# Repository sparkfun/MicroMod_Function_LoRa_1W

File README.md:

SparkFun MicroMod LoRa Function Board
========================================

[*SparkFun MicroMod LoRa Function Board (DEV-18573)*](https://www.sparkfun.com/products/18573)

The SparkFun MicroMod LoRa Function Board provides LoRA and LoRaWAN capabilities to your MicroMod project. It is intended to be used in conjunction with a MicroMod Processor Board and a MicroMod Main Board, which provides the electrical interface between a processor board and the Function Board(s).

The LoRa Function Board utilizes the 915M30S LoRa module from EBYTE, which is a 1W (30dBm) transceiver based around the SX1276 from Semtech. There is a robust edge mount RP-SMA connector for large LoRa (915MHz) antennas; with modification, a U.FL connector is also available. We've successfully tested a 12 miles line-of-sight transmission with this module (test was performed under ideal conditions; individual user results may vary).

With the MicroMod standardization, users no longer need to cross-reference schematics with datasheets, while fumbling around with jumper wires. Simply, match up the function board's M.2 edge connector to the slot of the M.2 connector on the main board and secure the function board with screws.

Repository Contents
-------------------

* **/Firmware** - Arduino example code from the tutorial
* **/Hardware** - Eagle design files (.brd, .sch)
* **/Hardware/Production** - Production panel files (.brd)

Documentation
--------------

* **[E19-915M30S Datasheet](https://github.com/sparkfun/MicroMod_Function_LoRa_1W/blob/main/Documents/E19-915M30S_Usermanual_EN_v1.20.pdf)** - Datasheet for the LoRa module
  * **[SX1276 Datasheet](https://cdn.sparkfun.com/assets/7/7/3/2/2/SX1276_Datasheet.pdf)** - Datasheet for the transceiver the LoRa module is based on
* **[Hookup Guide](https://learn.sparkfun.com/tutorials/1996)** - Basic hookup guide
* **[SparkFun External EEPROM Arduino Library](https://github.com/sparkfun/SparkFun_External_EEPROM_Arduino_Library)** - Arduino library for the EEPROM
* **[RadioLib Arduino Library](https://github.com/jgromes/RadioLib)** - Arduino library for peer-to-peer communication with the LoRa module

Product Versions
----------------

* [DEV-18573](https://www.sparkfun.com/products/18573)- Initial release

Version History
---------------

* v1.0 - Initial Release

License Information
-------------------

This product is _**open source**_! 

Please review the LICENSE.md file for license information. 

If you have any questions or concerns on licensing, please contact technical support on our [SparkFun forums](https://forum.sparkfun.com/viewforum.php?f=152).

Distributed as-is; no warranty is given.

- Your friends at SparkFun.

_<COLLABORATION CREDIT>_

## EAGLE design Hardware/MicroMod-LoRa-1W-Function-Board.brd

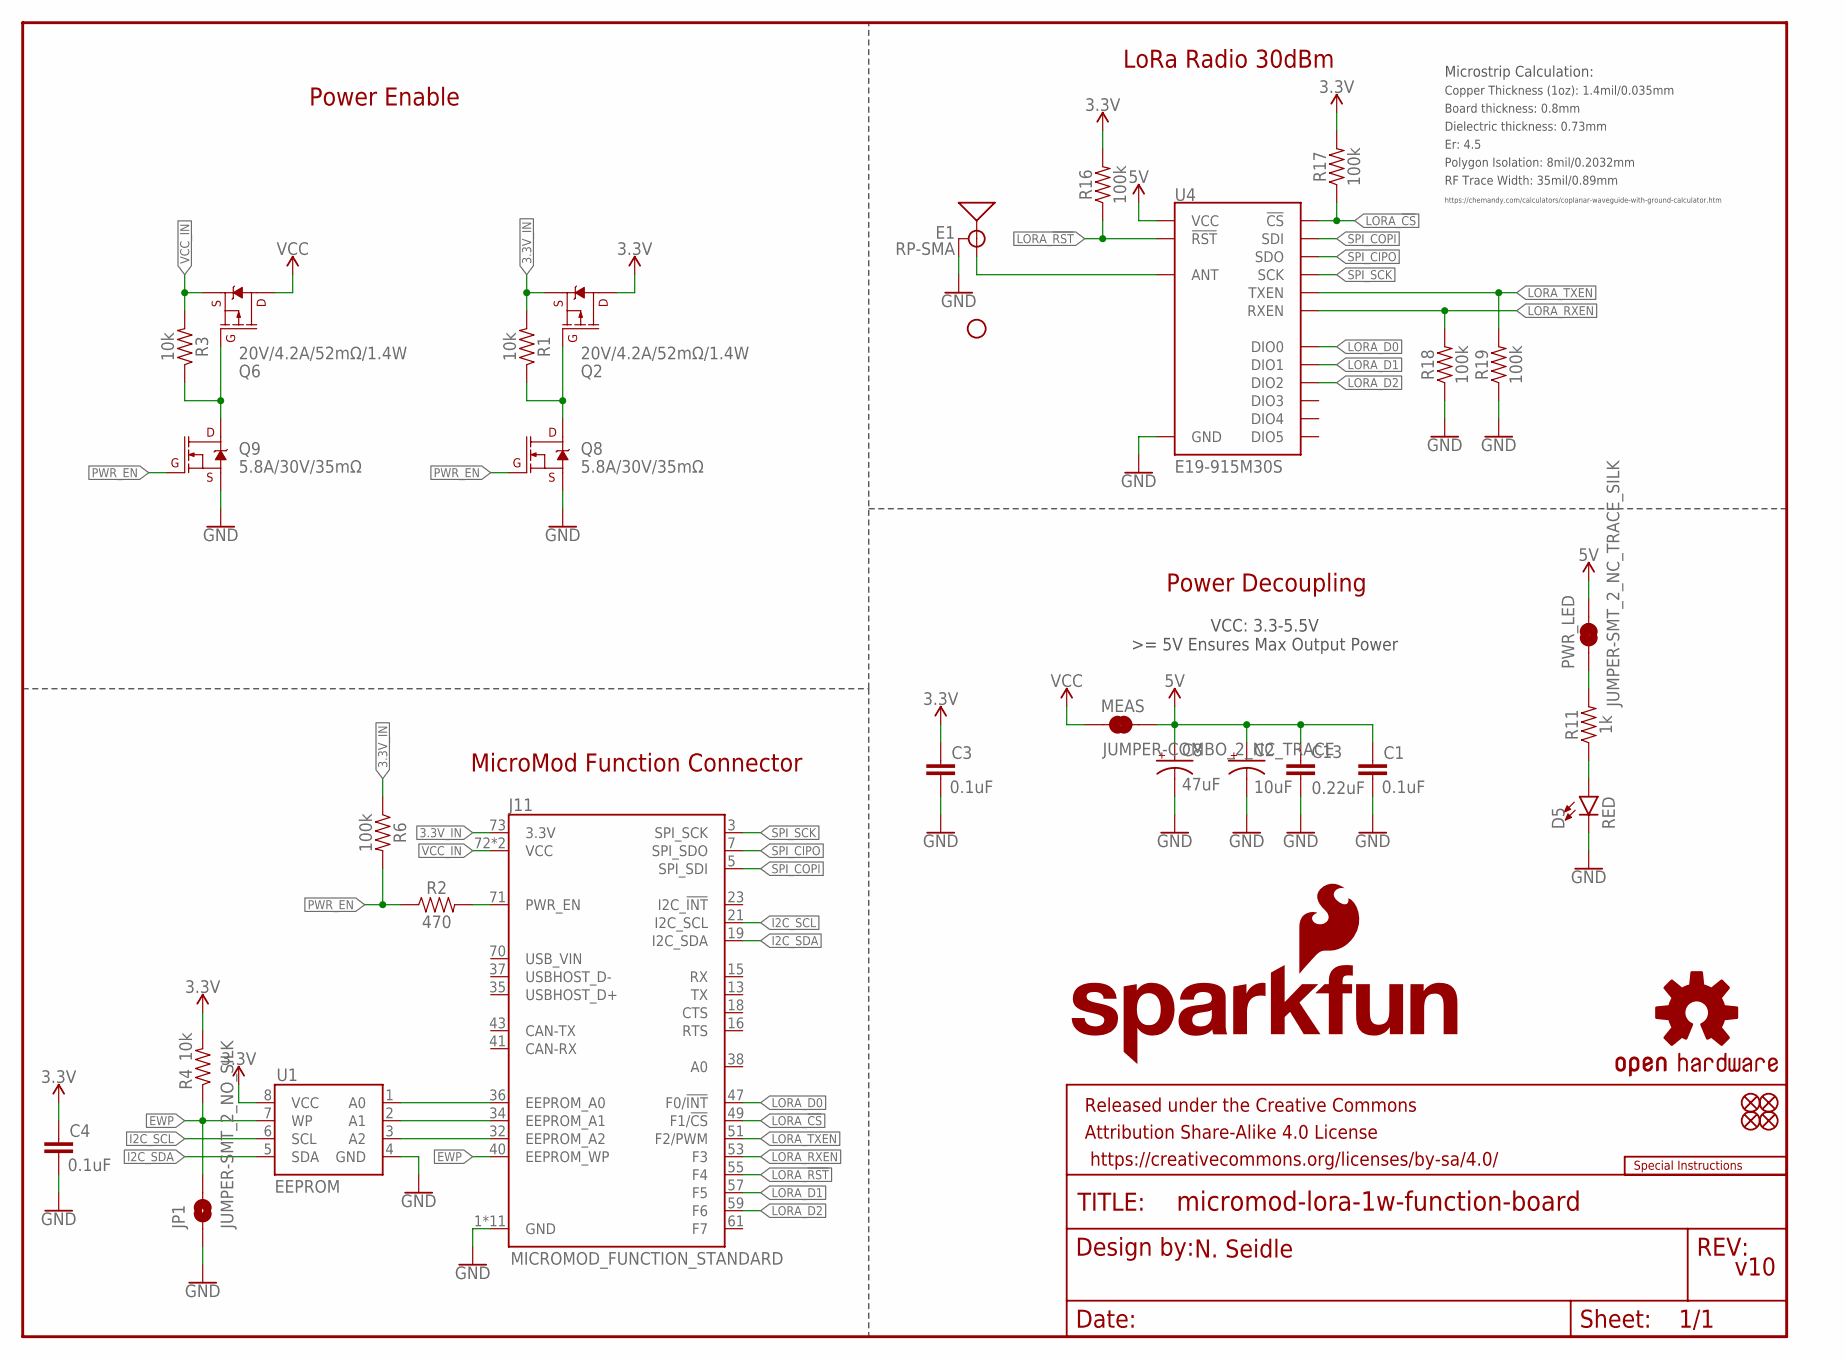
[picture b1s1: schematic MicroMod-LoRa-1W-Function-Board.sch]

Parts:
C1, C3, C4: 0.1uF; 0603
C2: 10uF; EIA3216
C8: 47uF; EIA3528
C13: 0.22uF; 0603
D5: RED; LED-0603
E1: RP-SMA; SMA-EDGE-SMD
FD1, FD2, FD3, FD4: FIDUCIALUFIDUCIAL; FIDUCIAL-MICRO
FRAME2: FRAME-LETTER; CREATIVE_COMMONS
H1: STAND-OFF
J11: MICROMOD_FUNCTION_STANDARD; M.2-CARD-E-22_FUNCTION_STANDARD
JP1: JUMPER-SMT_2_NO_SILK; SMT-JUMPER_2_NO_SILK
LOGO1: SFE_LOGO_NAME_FLAME.1_INCH; SFE_LOGO_NAME_FLAME_.1
LOGO2: SPECIAL_INSTRUCTIONS-ORDERING; ORDERING_INSTRUCTIONS
LOGO3: OSHW-LOGOMINI; OSHW-LOGO-MINI
MEAS: JUMPER-COMBO_2_NC_TRACE; COMBO-JUMPER_2_NC_TRACE
PWR_LED: JUMPER-SMT_2_NC_TRACE_SILK; SMT-JUMPER_2_NC_TRACE_SILK
Q2, Q6: 20V/4.2A/52mΩ/1.4W; SOT23-3
Q8, Q9: 5.8A/30V/35mΩ; SOT23-3
R1, R3, R4: 10k; 0603
R2: 470; 0603
R6, R16, R17, R18, R19: 100k; 0603
R11: 1k; 0603
U1: EEPROM; SO08
U4: E19-915M30S; E19-915MS1W

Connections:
3.3V: C3.1, C4.1, Q2.3 (D), R4.2, R16.2, R17.2, U1.8 (VCC)
3.3V_IN: J11.73 (3.3V), Q2.2 (S), R1.2, R6.1
5V: C1.1, C2.+, C8.A (+), C13.1, MEAS.2, MEAS.4 (2), PWR_LED.2, U4.11 (VCC)
A0: J11.36 (EEPROM_A0), U1.1 (A0)
A1: J11.34 (EEPROM_A1), U1.2 (A1)
A2: J11.32 (EEPROM_A2), U1.3 (A2)
EWP: J11.40 (EEPROM_WP), JP1.2, R4.1, U1.7 (WP)
GND: C1.2, C2.-, C3.2, C4.2, C8.C (-), C13.2, D5.C, E1.GND@0 (GND), E1.GND@1 (GND), J11.1 (GND), J11.33 (GND), J11.39 (GND), J11.45 (GND), J11.75 (GND), J11.GND1 (GND), J11.GND2 (GND), J11.GND3 (GND), J11.GND4 (GND), J11.GND5 (GND), J11.GND6 (GND), JP1.1, Q8.2 (S), Q9.2 (S), R18.1, R19.1, U1.4 (GND), U4.1 (GND), U4.9 (GND), U4.10 (GND), U4.18 (GND), U4.20 (GND), U4.21 (GND), U4.22 (GND)
I2C_SCL: J11.21 (I2C_SCL), U1.6 (SCL)
I2C_SDA: J11.19 (I2C_SDA), U1.5 (SDA)
LORA_!CS!: J11.49 (F1/!CS!), R17.1, U4.15 (!CS)
LORA_!RST!: J11.55 (F4), R16.1, U4.8 (!RST)
LORA_D0: J11.47 (F0/!INT!), U4.7 (DIO0)
LORA_D1: J11.57 (F5), U4.6 (DIO1)
LORA_D2: J11.59 (F6), U4.5 (DIO2)
LORA_RXEN: J11.53 (F3), R18.2, U4.17 (RXEN)
LORA_TXEN: J11.51 (F2/PWM), R19.2, U4.16 (TXEN)
unnamed: E1.SIG (SIGNAL), U4.19 (ANT)
unnamed: Q2.1 (G), Q8.3 (D), R1.1
unnamed: Q6.1 (G), Q9.3 (D), R3.1
unnamed: J11.71 (PWR_EN), R2.2
unnamed: D5.A, R11.1
unnamed: PWR_LED.1, R11.2
PWR_EN: Q8.1 (G), Q9.1 (G), R2.1, R6.2
SPI_CIPO: J11.7 (SPI_SDO), U4.13 (SDO)
SPI_COPI: J11.5 (SPI_SDI), U4.14 (SDI)
SPI_SCK: J11.3 (SPI_SCK), U4.12 (SCK)
VCC: MEAS.1, MEAS.3 (1), Q6.3 (D)
VCC_IN: J11.72 (VCC), J11.74 (VCC), Q6.2 (S), R3.2

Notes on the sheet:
Power Decoupling
MicroMod Function Connector
VCC: 3.3-5.5V >= 5V Ensures Max Output Power
N. Seidle
v10
LoRa Radio 30dBm
Board thickness: 0.8mm
Er: 4.5
Copper Thickness (1oz): 1.4mil/0.035mm
RF Trace Width: 35mil/0.89mm
Polygon Isolation: 8mil/0.2032mm
Dielectric thickness: 0.73mm
https://chemandy.com/calculators/coplanar-waveguide-with-ground-calculator.htm
Microstrip Calculation:
Power Enable

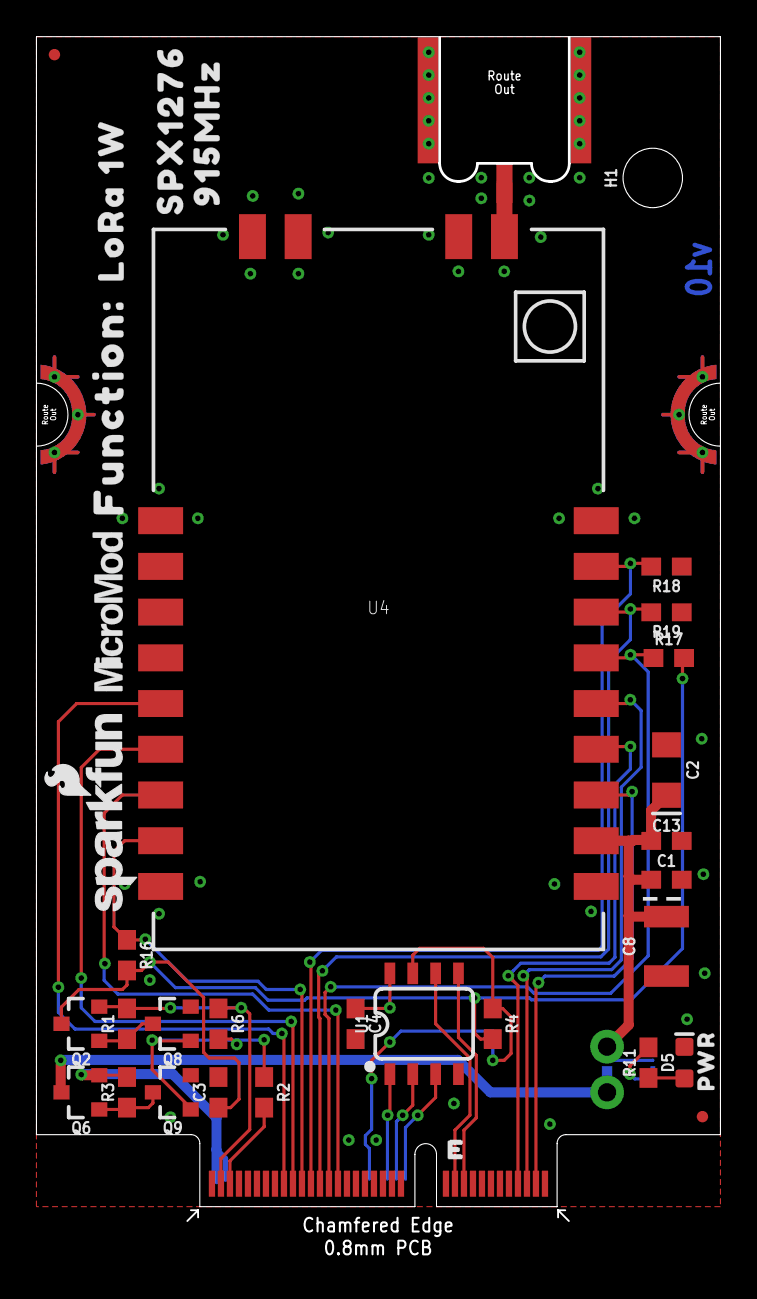
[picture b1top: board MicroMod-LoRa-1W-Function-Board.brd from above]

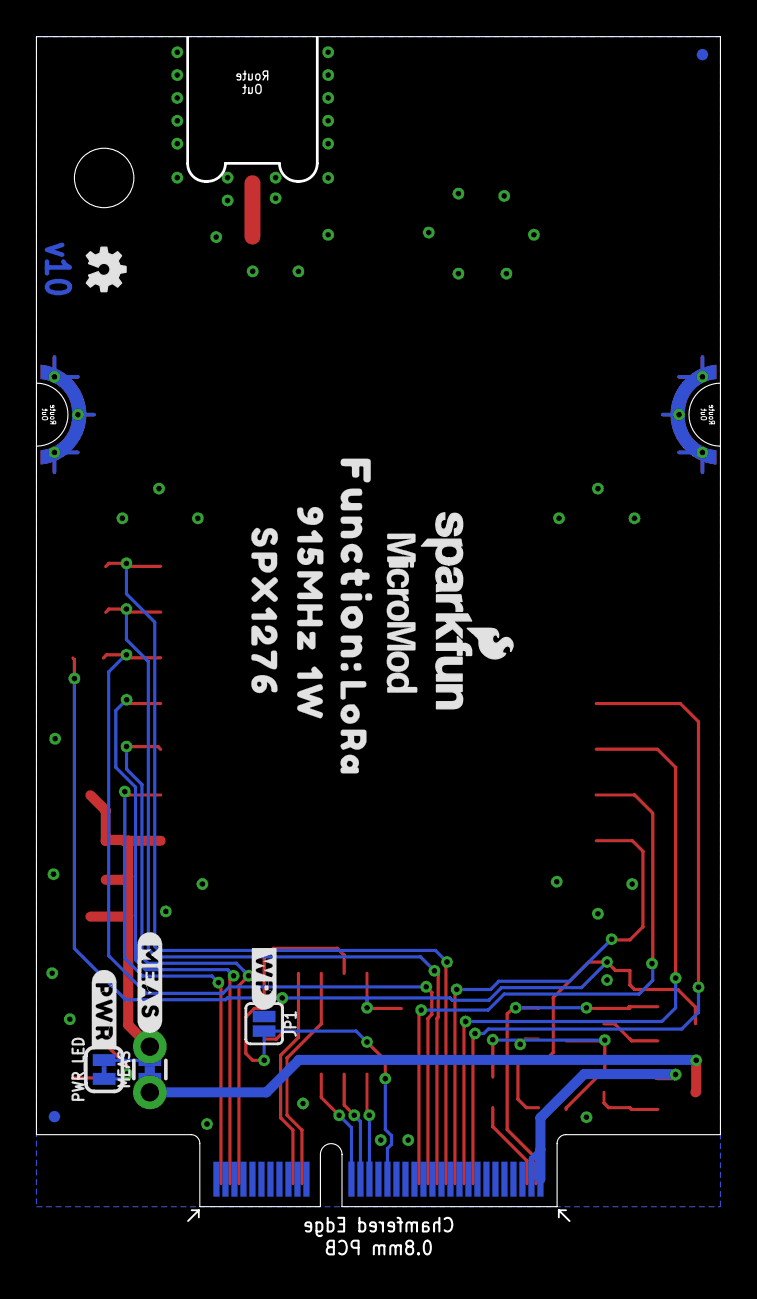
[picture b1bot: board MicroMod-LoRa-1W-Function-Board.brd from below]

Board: 2 copper layers, 37.9 x 68.0 mm, 54 parts (16 on the bottom side), 29 nets.

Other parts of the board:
LOGO4: SFE_LOGO_NAME_FLAME.1_INCH; SFE_LOGO_NAME_FLAME_.1
U$1, U$5: LORA0
U$2, U$30: 1W1
U$3, U$29: 915MHZ2
U$4, U$8: FUNCTION#0
U$6, U$27: SPX12763
U$7: PWR0
U$9: #PWR#0
U$10: #WP#0
U$28: #MEAS#3
U$37, U$63: MICROMOD_LOGO_.35

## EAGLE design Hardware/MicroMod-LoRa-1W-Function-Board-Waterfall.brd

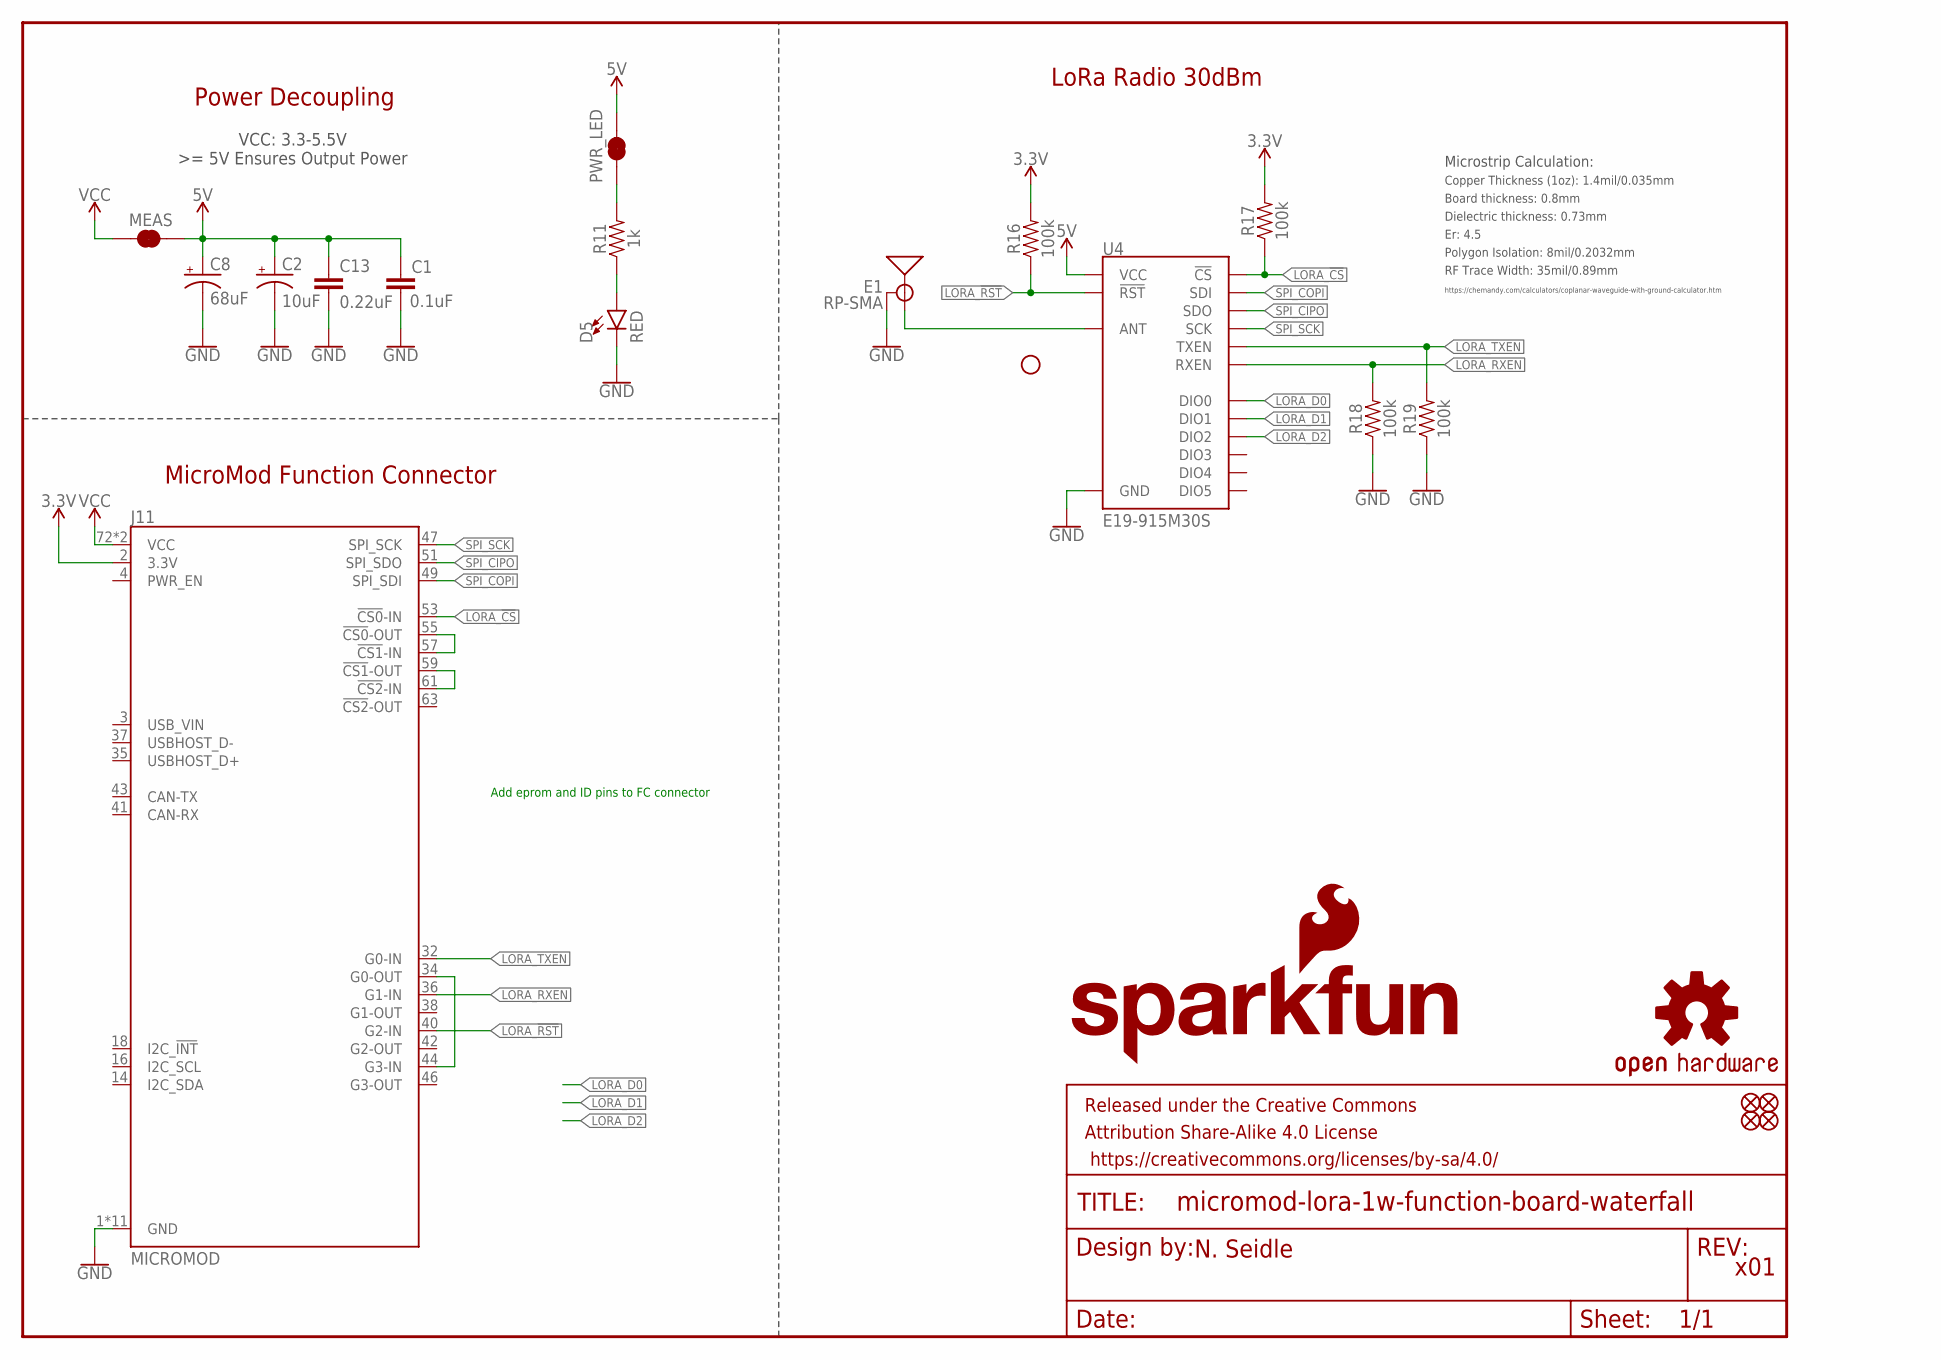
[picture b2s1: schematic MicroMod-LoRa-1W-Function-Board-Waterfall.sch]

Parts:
C1: 0.1uF; 0603
C2: 10uF; EIA3216
C8: 68uF; EIA3528
C13: 0.22uF; 0603
D5: RED; LED-0603
E1: RP-SMA; SMA-EDGE-SMD
FD1, FD2, FD3, FD4: FIDUCIALUFIDUCIAL; FIDUCIAL-MICRO
FRAME2: FRAME-LETTER; CREATIVE_COMMONS
H1: STAND-OFF
J11: MICROMOD; M.2-CARD-E-22_FUNCTION_STANDARD
LOGO1: SFE_LOGO_NAME_FLAME.1_INCH; SFE_LOGO_NAME_FLAME_.1
LOGO3: OSHW-LOGOMINI; OSHW-LOGO-MINI
MEAS: JUMPER-COMBO_2_NC_TRACE; COMBO-JUMPER_2_NC_TRACE
PWR_LED: JUMPER-SMT_2_NC_TRACE_SILK; SMT-JUMPER_2_NC_TRACE_SILK
R11: 1k; 0603
R16, R17, R18, R19: 100k; 0603
U4: E19-915M30S; E19-915MS1W

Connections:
3.3V: J11.2 (3.3V), R16.2, R17.2
5V: C1.1, C2.+, C8.A (+), C13.1, MEAS.2, MEAS.4 (2), PWR_LED.2, U4.11 (VCC)
GND: C1.2, C2.-, C8.C (-), C13.2, D5.C, E1.GND@0 (GND), E1.GND@1 (GND), J11.1 (GND), J11.33 (GND), J11.39 (GND), J11.45 (GND), J11.75 (GND), J11.GND1 (GND), J11.GND2 (GND), J11.GND3 (GND), J11.GND4 (GND), J11.GND5 (GND), J11.GND6 (GND), R18.1, R19.1, U4.1 (GND), U4.9 (GND), U4.10 (GND), U4.18 (GND), U4.20 (GND), U4.21 (GND), U4.22 (GND)
LORA_!CS!: J11.53 (!CS0!-IN), R17.1, U4.15 (!CS)
LORA_!RST!: J11.40 (G2-IN), R16.1, U4.8 (!RST)
LORA_D0: U4.7 (DIO0)
LORA_D1: U4.6 (DIO1)
LORA_D2: U4.5 (DIO2)
LORA_RXEN: J11.36 (G1-IN), R18.2, U4.17 (RXEN)
LORA_TXEN: J11.32 (G0-IN), R19.2, U4.16 (TXEN)
unnamed: E1.SIG (SIGNAL), U4.19 (ANT)
unnamed: J11.55 (!CS0!-OUT), J11.57 (!CS1!-IN)
unnamed: J11.59 (!CS1!-OUT), J11.61 (!CS2!-IN)
unnamed: J11.34 (G0-OUT), J11.44 (G3-IN)
unnamed: D5.A, R11.1
unnamed: PWR_LED.1, R11.2
SPI_CIPO: J11.51 (SPI_SDO), U4.13 (SDO)
SPI_COPI: J11.49 (SPI_SDI), U4.14 (SDI)
SPI_SCK: J11.47 (SPI_SCK), U4.12 (SCK)
VCC: J11.72 (VCC), J11.74 (VCC), MEAS.1, MEAS.3 (1)

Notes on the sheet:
Power Decoupling
MicroMod Function Connector
VCC: 3.3-5.5V >= 5V Ensures Output Power
N. Seidle
x01
LoRa Radio 30dBm
Board thickness: 0.8mm
Er: 4.5
Copper Thickness (1oz): 1.4mil/0.035mm
RF Trace Width: 35mil/0.89mm
Polygon Isolation: 8mil/0.2032mm
Dielectric thickness: 0.73mm
https://chemandy.com/calculators/coplanar-waveguide-with-ground-calculator.htm
Microstrip Calculation:
Add eprom and ID pins to FC connector

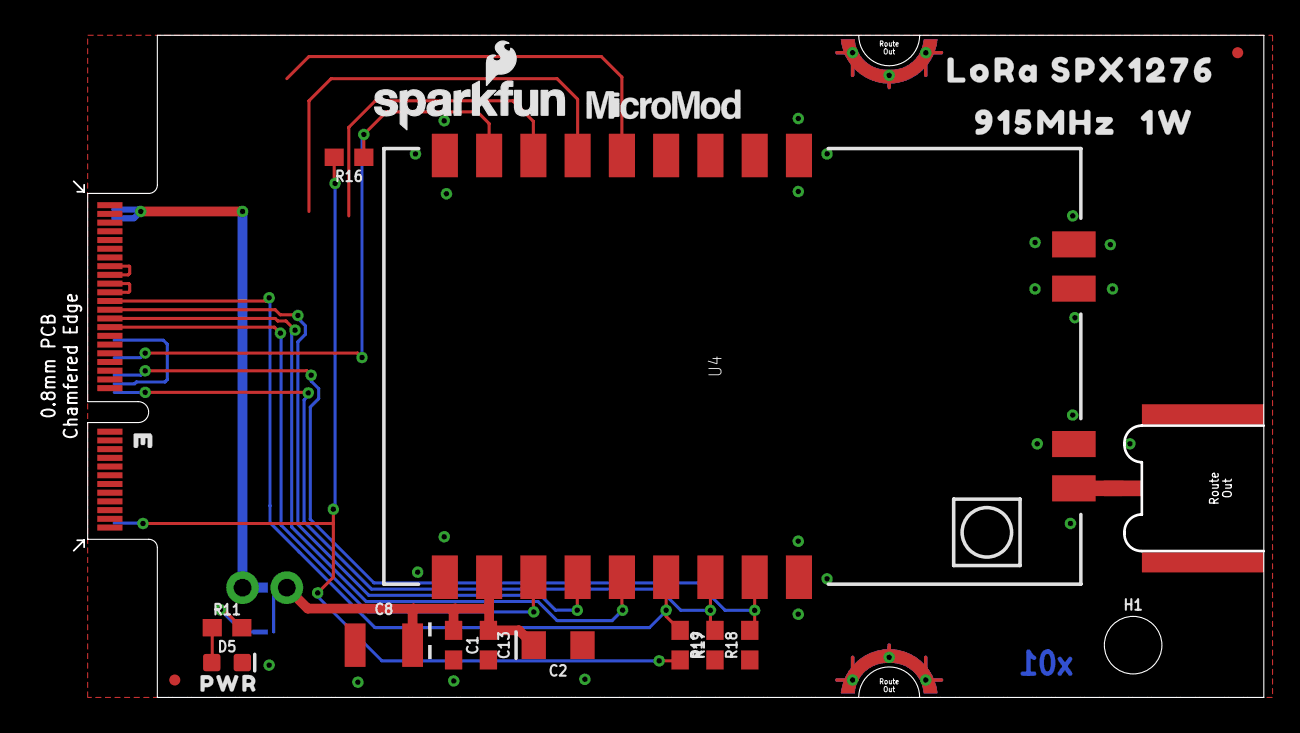
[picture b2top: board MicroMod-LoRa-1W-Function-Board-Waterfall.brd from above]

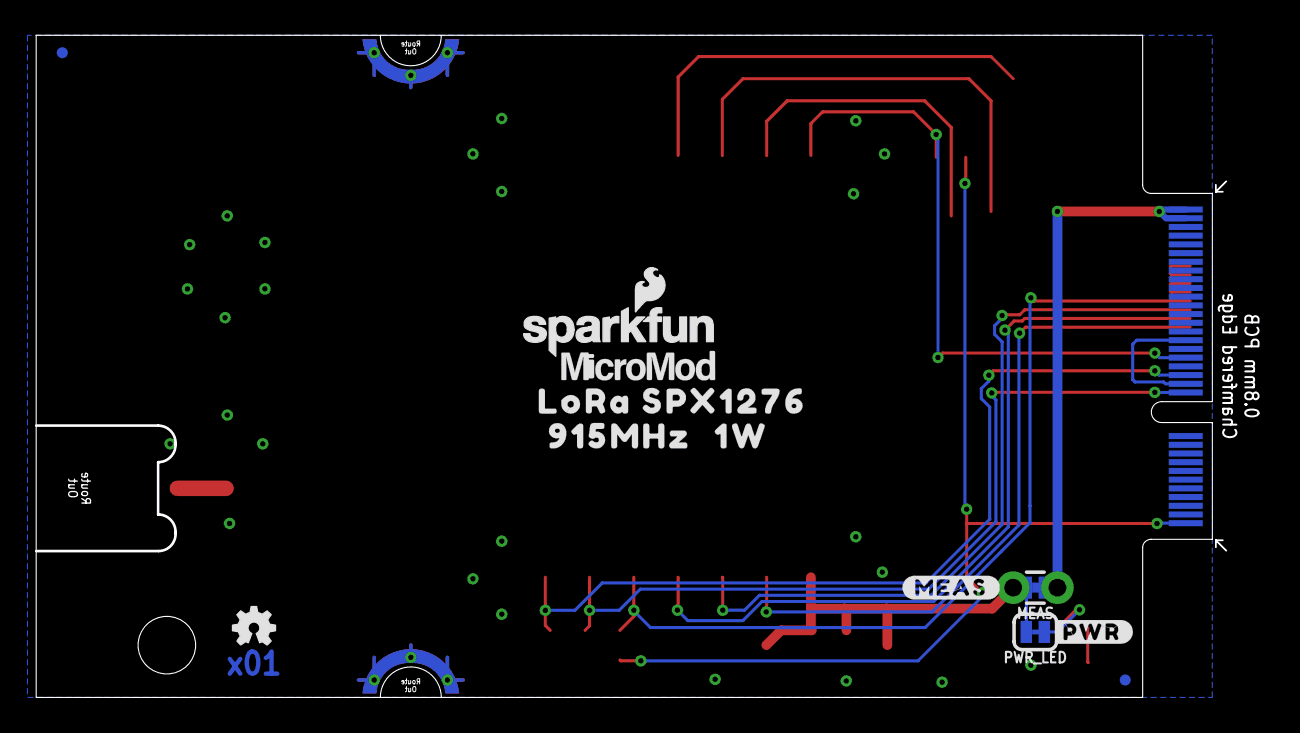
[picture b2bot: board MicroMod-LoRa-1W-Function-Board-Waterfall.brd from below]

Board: 2 copper layers, 70.5 x 37.9 mm, 37 parts (13 on the bottom side), 17 nets.

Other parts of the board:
LOGO4: SFE_LOGO_NAME_FLAME.1_INCH; SFE_LOGO_NAME_FLAME_.1
U$1, U$5: LORA0
U$2, U$30: 1W1
U$3, U$29: 915MHZ2
U$4: #PWR#0
U$6, U$27: SPX12763
U$7: PWR0
U$28: #MEAS#3
U$37, U$63: MICROMOD_LOGO_.35

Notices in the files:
parts and their libraries:
SparkFun-Aesthetics: Licensing: Creative Commons ShareAlike 4.0 International - https://creativecommons.org/licenses/by-sa/4.0
SparkFun-Aesthetics: Released under the Creative Commons Attribution Share-Alike 4.0 License
SparkFun-Aesthetics: https://creativecommons.org/licenses/by-sa/4.0
